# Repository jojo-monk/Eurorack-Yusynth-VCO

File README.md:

# Eurorack-Yusynth-VCO
Adaptation eurorack du yusynth VCO

pas encore testé

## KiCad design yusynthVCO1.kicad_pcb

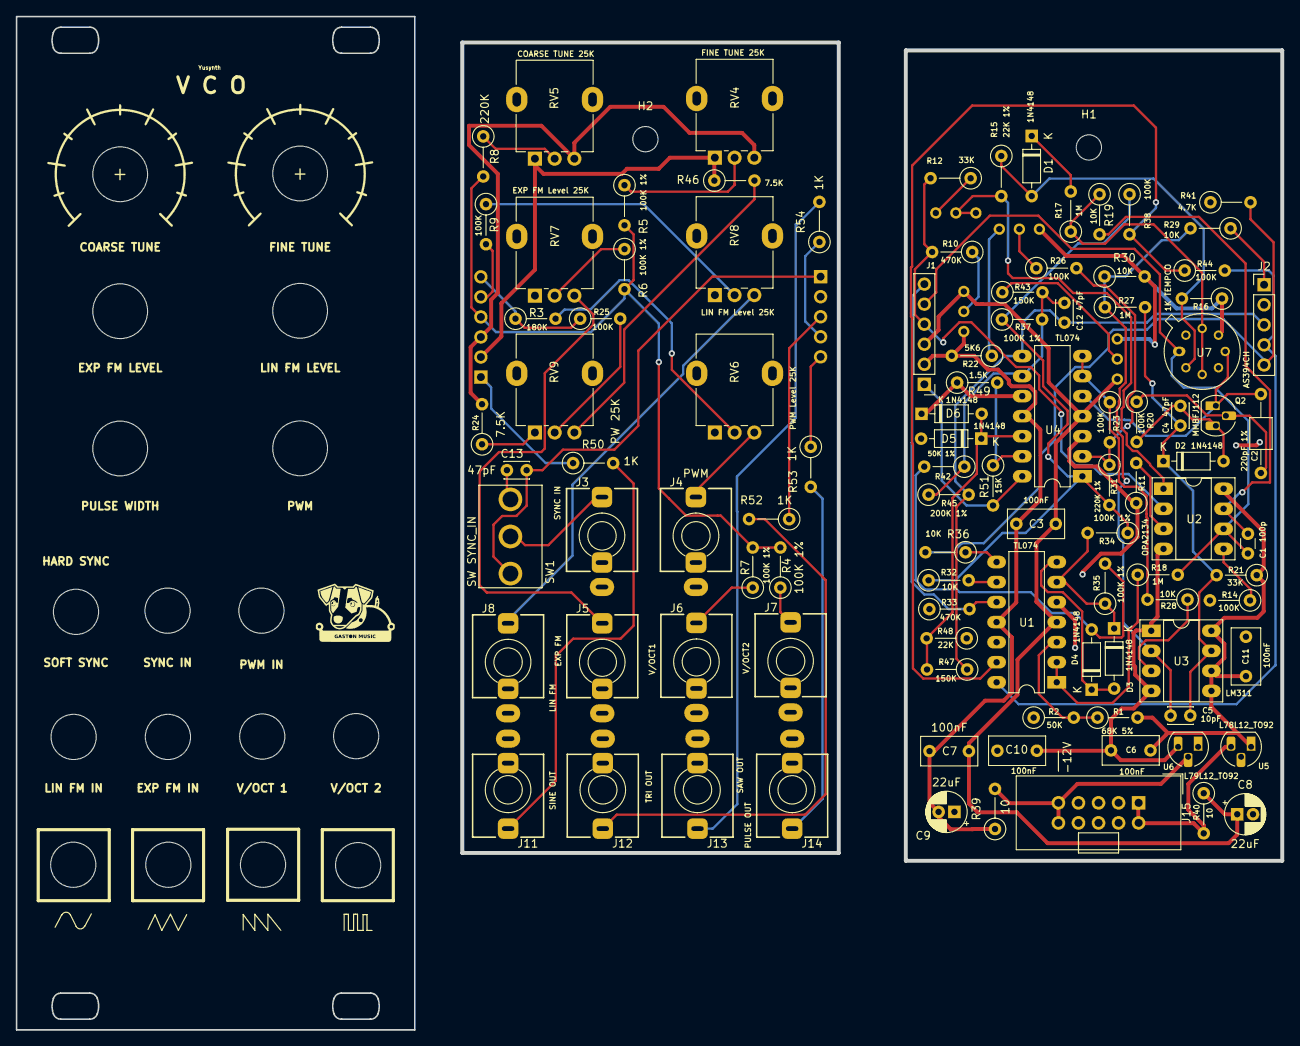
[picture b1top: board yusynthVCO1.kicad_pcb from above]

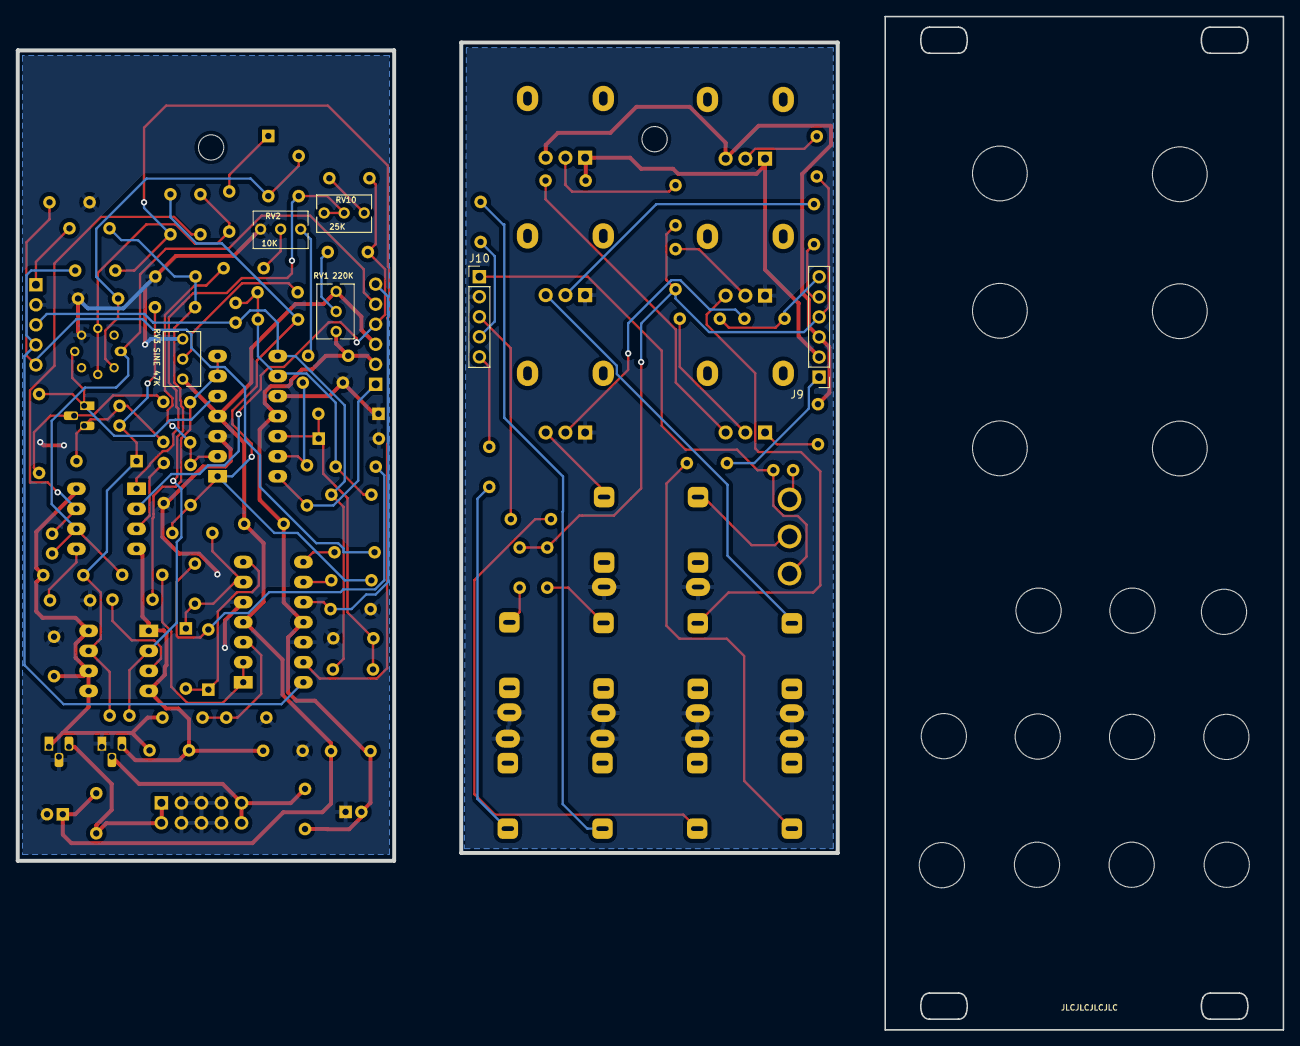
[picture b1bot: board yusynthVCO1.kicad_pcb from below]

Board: 2 copper layers, 160.2 x 128.1 mm, 108 parts (6 on the bottom side), 74 nets.

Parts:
C1: 100p; C_Disc_D3.0mm_W1.6mm_P2.50mm
C2: 220pF 1%; C_Axial_L3.8mm_D2.6mm_P10.00mm_Horizontal
C3, C6, C7, C10, C11: 100nF; C_Rect_L7.0mm_W3.5mm_P5.00mm
C4, C12, C13: 47pF; C_Disc_D3.0mm_W2.0mm_P2.50mm
C5: 10pF; C_Disc_D3.0mm_W2.0mm_P2.50mm
C8, C9: 22uF; CP_Radial_D5.0mm_P2.00mm
D1, D2, D3, D4, D5, D6: 1N4148; D_DO-35_SOD27_P7.62mm_Horizontal
H1, H2: MountingHole; MountingHole_3.2mm_M3
J1: Conn_01x6_Male_MainB; PinHeader_1x06_P2.54mm_Vertical
J2: Conn_01x5_Male_MainB; PinHeader_1x05_P2.54mm_Vertical
J3: SYNC IN; Jack_3.5mm_QingPu_WQP-PJ398SM_Vertical
J4: PWM; Jack_3.5mm_QingPu_WQP-PJ398SM_Vertical
J5: EXP FM; Jack_3.5mm_QingPu_WQP-PJ398SM_Vertical
J6: V/OCT1; Jack_3.5mm_QingPu_WQP-PJ398SM_Vertical
J7: V/OCT2; Jack_3.5mm_QingPu_WQP-PJ398SM_Vertical
J8: LIN FM; Jack_3.5mm_QingPu_WQP-PJ398SM_Vertical
J9: Conn_01x6_Female_CtrlB; PinHeader_1x06_P2.54mm_Vertical
J10: Conn_01x5_Female_CtrlB; PinHeader_1x05_P2.54mm_Vertical
J11: SINE OUT; Jack_3.5mm_QingPu_WQP-PJ398SM_Vertical
J12: TRI OUT; Jack_3.5mm_QingPu_WQP-PJ398SM_Vertical
J13: SAW OUT; Jack_3.5mm_QingPu_WQP-PJ398SM_Vertical
J14: PULSE OUT; Jack_3.5mm_QingPu_WQP-PJ398SM_Vertical
J15: EURO_PWR_2x5; Eurorack_power_header
Q2: MMBFJ112; TO-92L_HandSolder
R1: 68K 5%; R_Axial_DIN0207_L6.3mm_D2.5mm_P5.08mm_Vertical
R2: 50K; R_Axial_DIN0207_L6.3mm_D2.5mm_P5.08mm_Vertical
R3: 180K; R_Axial_DIN0207_L6.3mm_D2.5mm_P5.08mm_Vertical
R4, R5, R6, R7, R34, R35, R37: 100K 1%; R_Axial_DIN0207_L6.3mm_D2.5mm_P5.08mm_Vertical
R8: 220K; R_Axial_DIN0207_L6.3mm_D2.5mm_P5.08mm_Vertical
R9, R14, R20, R23, R25, R26, R38, R44: 100K; R_Axial_DIN0207_L6.3mm_D2.5mm_P5.08mm_Vertical
R10, R33: 470K; R_Axial_DIN0207_L6.3mm_D2.5mm_P5.08mm_Vertical
R11: 47K; R_Axial_DIN0207_L6.3mm_D2.5mm_P5.08mm_Vertical
R12, R21: 33K; R_Axial_DIN0207_L6.3mm_D2.5mm_P5.08mm_Vertical
R15: 22K 1%; R_Axial_DIN0207_L6.3mm_D2.5mm_P5.08mm_Vertical
R16: 1K TEMPCO; R_Axial_DIN0207_L6.3mm_D2.5mm_P5.08mm_Vertical
R17, R18, R27: 1M; R_Axial_DIN0207_L6.3mm_D2.5mm_P5.08mm_Vertical
R19, R28, R29, R30, R32, R36: 10K; R_Axial_DIN0207_L6.3mm_D2.5mm_P5.08mm_Vertical
R22: 5K6; R_Axial_DIN0207_L6.3mm_D2.5mm_P5.08mm_Vertical
R24, R46: 7.5K; R_Axial_DIN0207_L6.3mm_D2.5mm_P5.08mm_Vertical
R31: 220K 1%; R_Axial_DIN0207_L6.3mm_D2.5mm_P5.08mm_Vertical
R39, R40: 10; R_Axial_DIN0207_L6.3mm_D2.5mm_P5.08mm_Vertical
R41: 4.7K; R_Axial_DIN0207_L6.3mm_D2.5mm_P5.08mm_Vertical
R42: 50K 1%; R_Axial_DIN0207_L6.3mm_D2.5mm_P5.08mm_Vertical
R43, R47: 150K; R_Axial_DIN0207_L6.3mm_D2.5mm_P5.08mm_Vertical
R45: 200K 1%; R_Axial_DIN0207_L6.3mm_D2.5mm_P5.08mm_Vertical
R48: 22K; R_Axial_DIN0207_L6.3mm_D2.5mm_P5.08mm_Vertical
R49: 1.5K; R_Axial_DIN0207_L6.3mm_D2.5mm_P5.08mm_Vertical
R50, R52, R53, R54: 1K; R_Axial_DIN0207_L6.3mm_D2.5mm_P5.08mm_Vertical
R51: 15K; R_Axial_DIN0207_L6.3mm_D2.5mm_P5.08mm_Vertical
RV1: 220K; Potentiometer_Bourns_3266Y_Vertical
RV2: 10K; Potentiometer_Bourns_3266Y_Vertical
RV3: SINE 47K; Potentiometer_Bourns_3266Y_Vertical
RV4: FINE TUNE 25K; Potentiometer_Alpha_RD901F-40-00D_Single_Vertical
RV5: COARSE TUNE 25K; Potentiometer_Alpha_RD901F-40-00D_Single_Vertical
RV6: PWM Level 25K; Potentiometer_Alpha_RD901F-40-00D_Single_Vertical
RV7: EXP FM Level 25K; Potentiometer_Alpha_RD901F-40-00D_Single_Vertical
RV8: LIN FM Level 25K; Potentiometer_Alpha_RD901F-40-00D_Single_Vertical
RV9: PW 25K; Potentiometer_Alpha_RD901F-40-00D_Single_Vertical
RV10: 25K; Potentiometer_Bourns_3266Y_Vertical
SW1: SW SYNC_IN; SPDT toggle on-off-on
U1, U4: TL074; DIP-14_W7.62mm_LongPads
U2: OPA2134; DIP-8_W7.62mm_Socket_LongPads
U3: LM311; DIP-8_W7.62mm_Socket_LongPads
U5: L78L12_TO92; TO-92L_HandSolder
U6: L79L12_TO92; TO-92L_HandSolder
U7: AS394CH; TO-5-8

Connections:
+12V: C3.1, C7.1, C8.1, J1.3, J9.3, R24.2, R40.1, RV1.3, RV3.1, RV4.3, RV5.3, U1.4 (V+), U4.4 (V+)
-12V: C3.2, C7.2, C9.2, J1.2, J9.2, R22.2, R39.1, R46.1, RV1.1, RV4.1, RV5.1, U1.11 (V-), U4.11 (V-)
GND: C8.2, C9.1, C10.1, C11.2, D5.2 (A), D6.1 (K), J2.2, J3.S, J4.S, J5.S, J6.S, J7.S, J8.S, J10.2, J11.S, J12.S, J13.S, J14.S, J15.3 (GND), J15.4 (GND), J15.5 (GND), J15.6 (GND), J15.7 (GND), J15.8 (GND), R2.1, R11.1, R14.2, R16.1, R30.2, R33.1, R41.1, R48.1, R49.1, RV2.3, RV3.3, RV6.1, RV7.1, RV8.1, U1.5 (+), U1.12 (+), U4.3 (+), U4.10 (+), U5.2 (GND), U6.1 (GND), U7.7
HARD SYNC IN CtrlB: C13.1, J10.1, SW1.1 (A)
HARD SYNC IN MainB: J2.1, R29.1
INPUT PW CtrlB: J9.6, R3.1, R25.1
INPUT PW MainB: J1.6, R33.2, U1.10 (+)
INPUTx5 CtrlB: J9.4, R4.2, R5.2, R6.2, R7.2, R8.2
INPUTx5 MainB: J1.4, R10.2, R12.2, U2.2 (-)
LINEAR FM CtrlB: J9.5, R9.2
LINEAR FM MainB: C1.1, J1.5, R18.2, U2.6 (-), U7.2
unnamed: C1.2, R19.2, U2.7
unnamed: C2.1, Q2.1 (D), U4.5 (+), U7.6
unnamed: C2.2, Q2.2 (S), R20.1
unnamed: C4.1, C5.2, D2.1 (K), R21.2, R27.2, U3.7
unnamed: C4.2, D2.2 (A), Q2.3 (G), R20.2
unnamed: C5.1, R27.1, R29.2, R30.1, U3.2 (+)
unnamed: C12.1, R37.2, R42.1, R43.2, R45.1, U4.9 (-)
unnamed: C13.2, SW1.3 (C)
unnamed: D1.1 (K), R17.2
unnamed: D1.2 (A), R15.1, R16.2, U7.3
unnamed: D3.1 (K), R34.2, R35.1, U1.6 (-)
unnamed: D3.2 (A), D4.1 (K), U1.7
unnamed: D4.2 (A), R35.2, R42.2
unnamed: D5.1 (K), D6.2 (A), R47.2, R48.2, U4.12 (+)
unnamed: J3.T, SW1.2 (B)
unnamed: J4.T, RV6.3
unnamed: J5.T, RV7.3
unnamed: J6.T, R7.1
unnamed: J7.T, R4.1
unnamed: J8.T, RV8.3
unnamed: J11.T, R50.2
unnamed: J12.T, R52.2
unnamed: J13.T, R54.2
unnamed: J14.T, R53.2
unnamed: J15.1 (+12V), J15.2 (+12V), R40.2, U5.3 (VI)
unnamed: J15.9 (-12V), J15.10 (-12V), R39.2, U6.2 (VI)
unnamed: R1.1, R2.2, U1.3 (+)
unnamed: R3.2, RV6.2
unnamed: R5.1, RV4.2
unnamed: R6.1, RV7.2
unnamed: R8.1, RV5.2
unnamed: R9.1, RV8.2
unnamed: R10.1, RV1.2
unnamed: R11.2, U2.3 (+)
unnamed: R12.1, RV10.1
unnamed: R14.1, U2.5 (+)
unnamed: R15.2, RV10.2, RV10.3, U2.1
unnamed: R17.1, R19.1, U7.4, U7.8
unnamed: R18.1, U1.1, U1.2 (-)
unnamed: R22.1, RV2.1
unnamed: R23.1, R28.2, U4.6 (-), U4.7
unnamed: R23.2, R26.2, R31.1, U4.2 (-)
unnamed: R24.1, RV9.1
unnamed: R25.2, RV9.2
unnamed: R26.1, RV2.2
unnamed: R28.1, U3.3 (-)
unnamed: R31.2, R32.1, R34.1, R37.1, R38.1, U4.1
unnamed: R32.2, U1.9 (-)
unnamed: R36.1, U1.8
unnamed: R38.2, R44.1, U1.13 (-)
unnamed: R43.1, RV3.2
unnamed: R46.2, RV9.3
unnamed: R49.2, R51.1, U4.13 (-)
PULSE OUT CtrlB: J10.5, R53.1
PULSE OUT MainB: J2.5, R36.2, R41.2
SAW OUT CtrlB: J10.4, R54.1
SAW OUT MainB: J2.4, R44.2, U1.14
SINE OUT CtrlB: J9.1, R50.1
SINE OUT MainB: J1.1, R51.2, U4.14
TRI OUT CtrlB: J10.3, R52.1
TRI OUT MainB: C12.2, J2.3, R45.2, R47.1, U4.8
VCC: C6.1, C11.1, R1.2, R21.1, U2.8 (V+), U3.5 (BAL), U3.6 (STRB), U3.8 (V+), U5.1 (VO)
VEE: C6.2, C10.2, U2.4 (V-), U3.1 (GND), U3.4 (V-), U6.3 (VO)

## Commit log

2023-03-04 Version AS394CH
